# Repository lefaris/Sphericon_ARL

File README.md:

# Agile Robotics Lab | Sphericon

## Code
### BLE
To run Arduino code using bluetooth low energy connectivity, first install a BLE app such as LightBlue on the app store.  Upload ArdA_Demo.ino to one Arduino Nano 33 BLE, and ArdB_Demo.ino to another Arduino Nano 33 BLE.  Connect a bluetooth device to each Arduino using the LightBlue app.  Once connected, send 0x35 to each Arduino to begin oscillations.

###  No BLE
To run Arduino code without the bluetooth low energy connectivity, upload sphericon_stepper.ino to each Arduino.  As soon as the code is uploaded, the motor assembly will start to swing.  A mechanical switch to enable the start of the code will be added to the PCBs in a future version.

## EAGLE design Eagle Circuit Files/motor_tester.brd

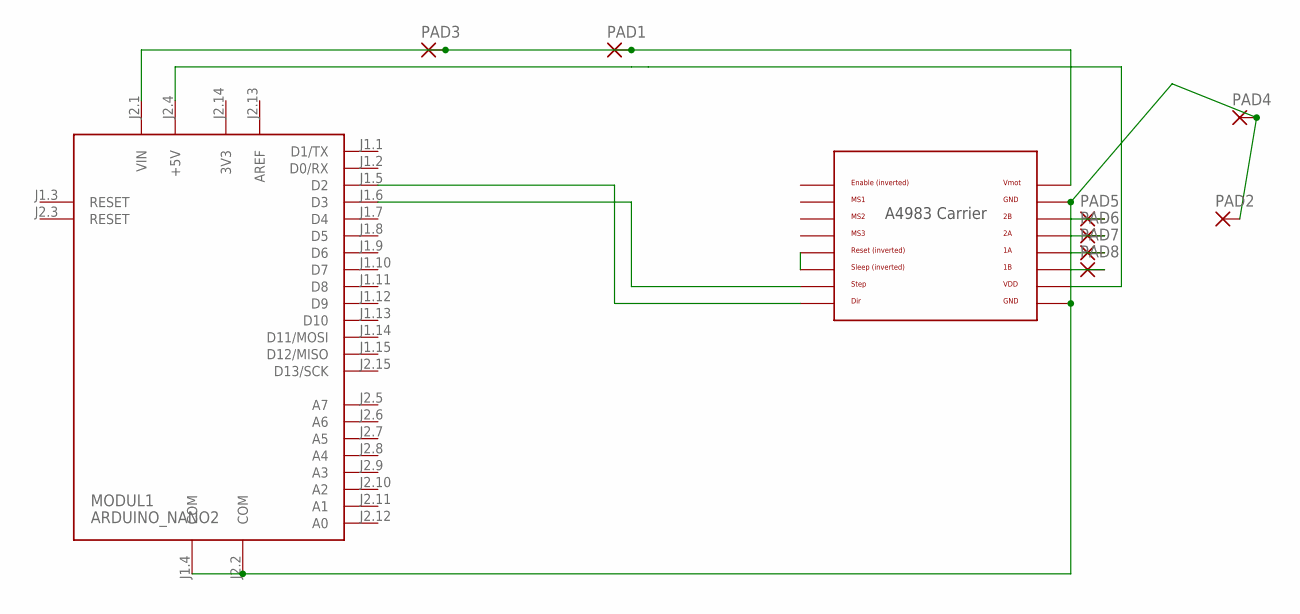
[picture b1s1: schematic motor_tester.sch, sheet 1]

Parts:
MODUL1: ARDUINO_NANO2
PAD1, PAD2, PAD3, PAD4, PAD5, PAD6, PAD7, PAD8: 1,6/0,8
U$6: POLOLU_A4983CARRIER; A4983CARRIER

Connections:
3V3: MODUL1.J2.14 (3V3)
AREF: MODUL1.J2.13 (AREF)
unnamed: MODUL1.J1.5 (D2), U$6.DIR
unnamed: MODUL1.J1.6 (D3), U$6.STEP
unnamed: MODUL1.J2.1 (VIN), PAD1.1, PAD3.1, U$6.VMOT
unnamed: U$6.RST, U$6.SLP (SLEEP)
unnamed: MODUL1.J1.4 (COM), MODUL1.J2.2 (COM), PAD2.1, PAD4.1, U$6.GND, U$6.GND@0 (GND)
unnamed: PAD5.1, U$6.2B
unnamed: PAD6.1, U$6.2A
unnamed: PAD7.1, U$6.1A
unnamed: PAD8.1, U$6.1B
unnamed: MODUL1.J2.4 (+5V), U$6.VDD

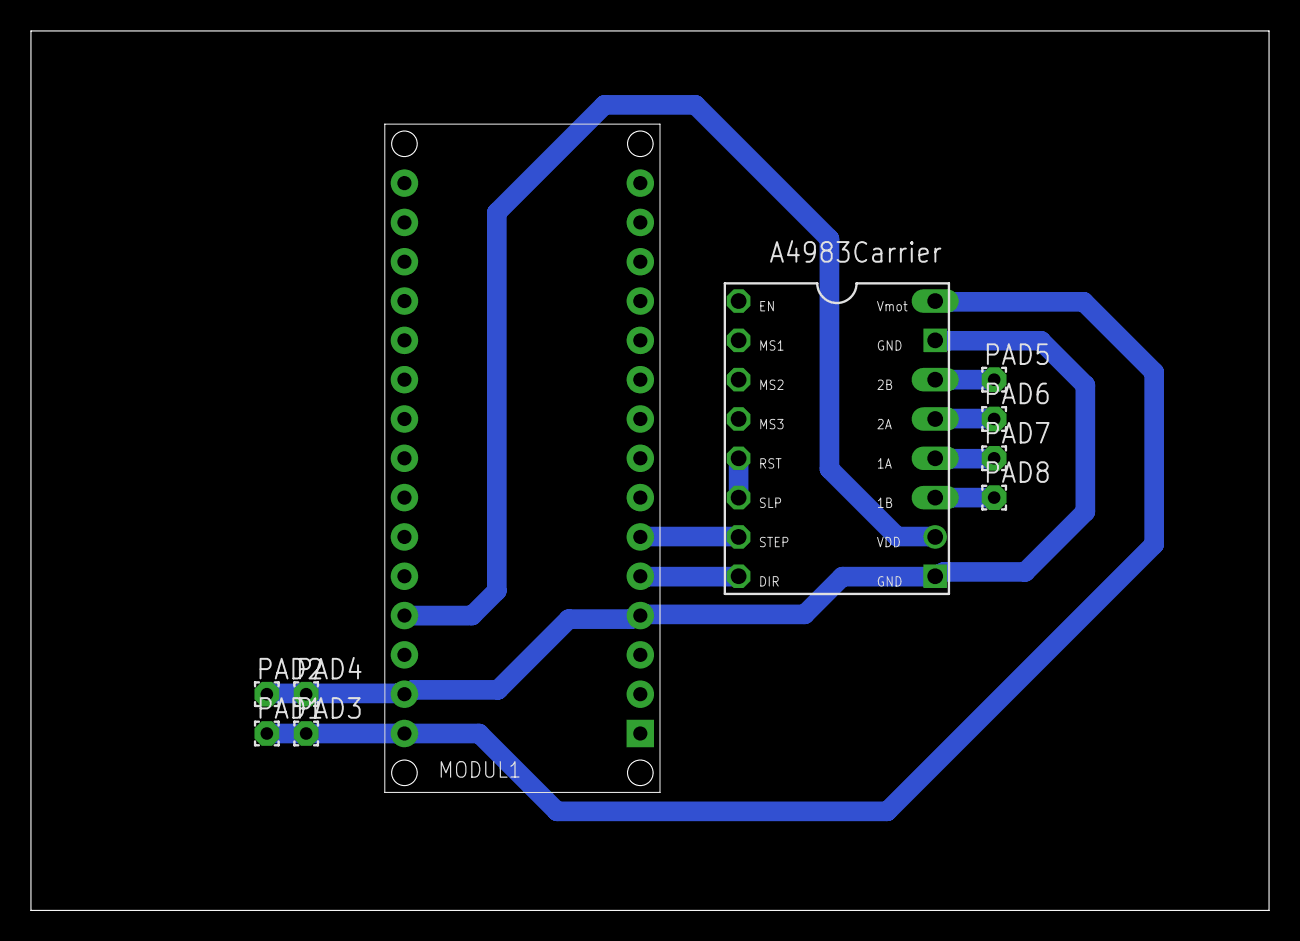
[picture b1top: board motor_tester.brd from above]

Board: 2 copper layers, 80.0 x 56.8 mm, 10 parts (0 on the bottom side), 10 nets.
